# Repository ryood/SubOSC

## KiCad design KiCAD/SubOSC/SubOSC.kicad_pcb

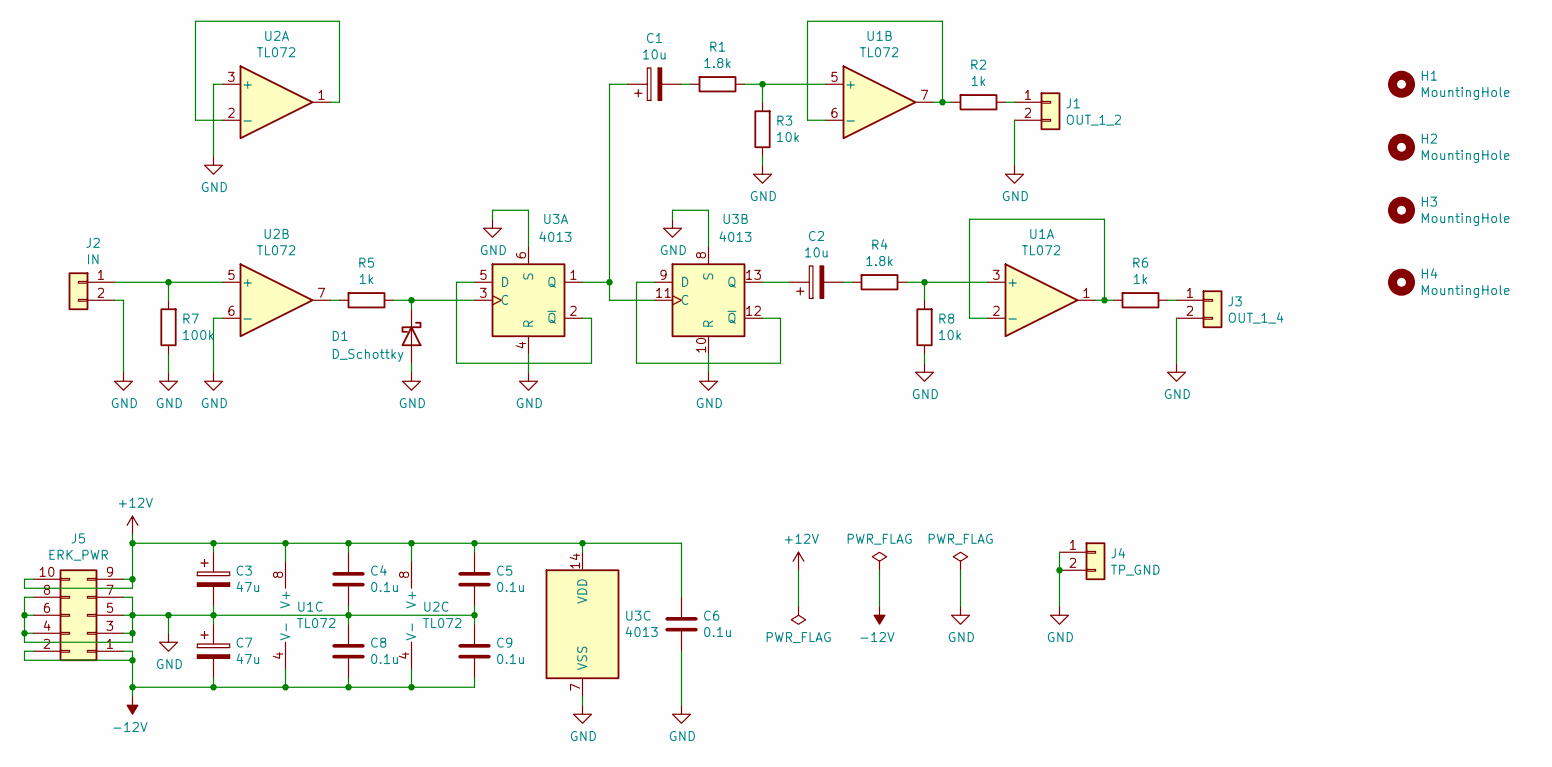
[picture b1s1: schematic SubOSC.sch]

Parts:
C1, C2: 10u; CP_Radial_D5.0mm_P2.50mm
C3, C7: 47u; CP_Radial_D5.0mm_P2.50mm
C4, C5, C6, C8, C9: 0.1u; C_Disc_D3.0mm_W1.6mm_P2.50mm
D1: D_Schottky; D_DO-35_SOD27_P10.16mm_Horizontal
H1, H2, H3, H4: MountingHole; MountingHole_3.2mm_M3
J1: OUT_1_2; JST_XH_B2B-XH-A_1x02_P2.50mm_Vertical
J2: IN; JST_XH_B2B-XH-A_1x02_P2.50mm_Vertical
J3: OUT_1_4; JST_XH_B2B-XH-A_1x02_P2.50mm_Vertical
J4: TP_GND; PinSocket_1x02_P2.54mm_Vertical
J5: ERK_PWR; IDC-Header_2x05_P2.54mm_Vertical
R1, R4: 1.8k; R_Axial_DIN0207_L6.3mm_D2.5mm_P10.16mm_Horizontal
R2, R5, R6: 1k; R_Axial_DIN0207_L6.3mm_D2.5mm_P10.16mm_Horizontal
R3, R8: 10k; R_Axial_DIN0207_L6.3mm_D2.5mm_P10.16mm_Horizontal
R7: 100k; R_Axial_DIN0207_L6.3mm_D2.5mm_P10.16mm_Horizontal
U1, U2: TL072; DIP-8_W7.62mm
U3: 4013; DIP-14_W7.62mm

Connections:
+12V: C3.1, C4.1, C5.1, C6.1, J5.9, J5.10, U1.8 (V+), U2.8 (V+), U3.14 (VDD)
-12V: C7.2, C8.2, C9.2, J5.1, J5.2, U1.4 (V-), U2.4 (V-)
GND: C3.2, C4.2, C5.2, C6.2, C7.1, C8.1, C9.1, D1.2 (A), J1.2, J2.2, J3.2, J4.1, J4.2, J5.3, J5.4, J5.5, J5.6, J5.7, J5.8, R3.1, R7.1, R8.1, U2.3 (+), U2.6 (-), U3.4 (R), U3.6 (S), U3.7 (VSS), U3.8 (S), U3.10 (R)
unnamed: C1.1, U3.1 (Q), U3.11 (C)
unnamed: C1.2, R1.2
unnamed: C2.1, U3.13 (Q)
unnamed: C2.2, R4.2
unnamed: D1.1 (K), R5.1, U3.3 (C)
unnamed: J1.1, R2.1
unnamed: J2.1, R7.2, U2.5 (+)
unnamed: J3.1, R6.1
unnamed: R1.1, R3.2, U1.5 (+)
unnamed: R2.2, U1.6 (-), U1.7
unnamed: R4.1, R8.2, U1.3 (+)
unnamed: R5.2, U2.7
unnamed: R6.2, U1.1, U1.2 (-)
unnamed: U2.1, U2.2 (-)
unnamed: U3.2 (~Q), U3.5 (D)
unnamed: U3.9 (D), U3.12 (~Q)

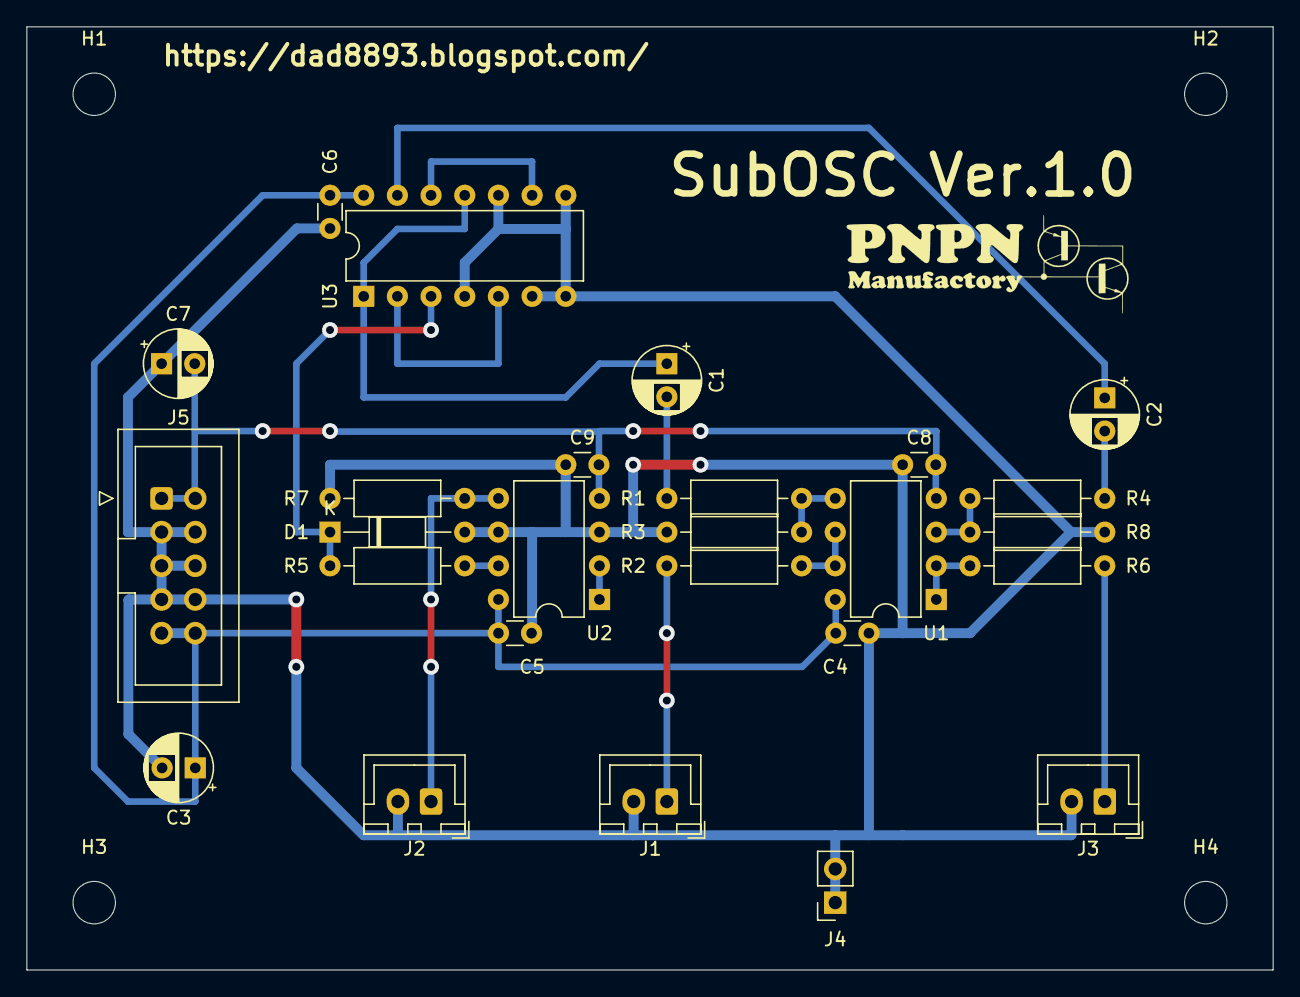
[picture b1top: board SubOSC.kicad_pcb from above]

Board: 2 copper layers, 94.0 x 71.1 mm, 30 parts (0 on the bottom side), 19 nets.

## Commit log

2021-10-10 Panel mount
